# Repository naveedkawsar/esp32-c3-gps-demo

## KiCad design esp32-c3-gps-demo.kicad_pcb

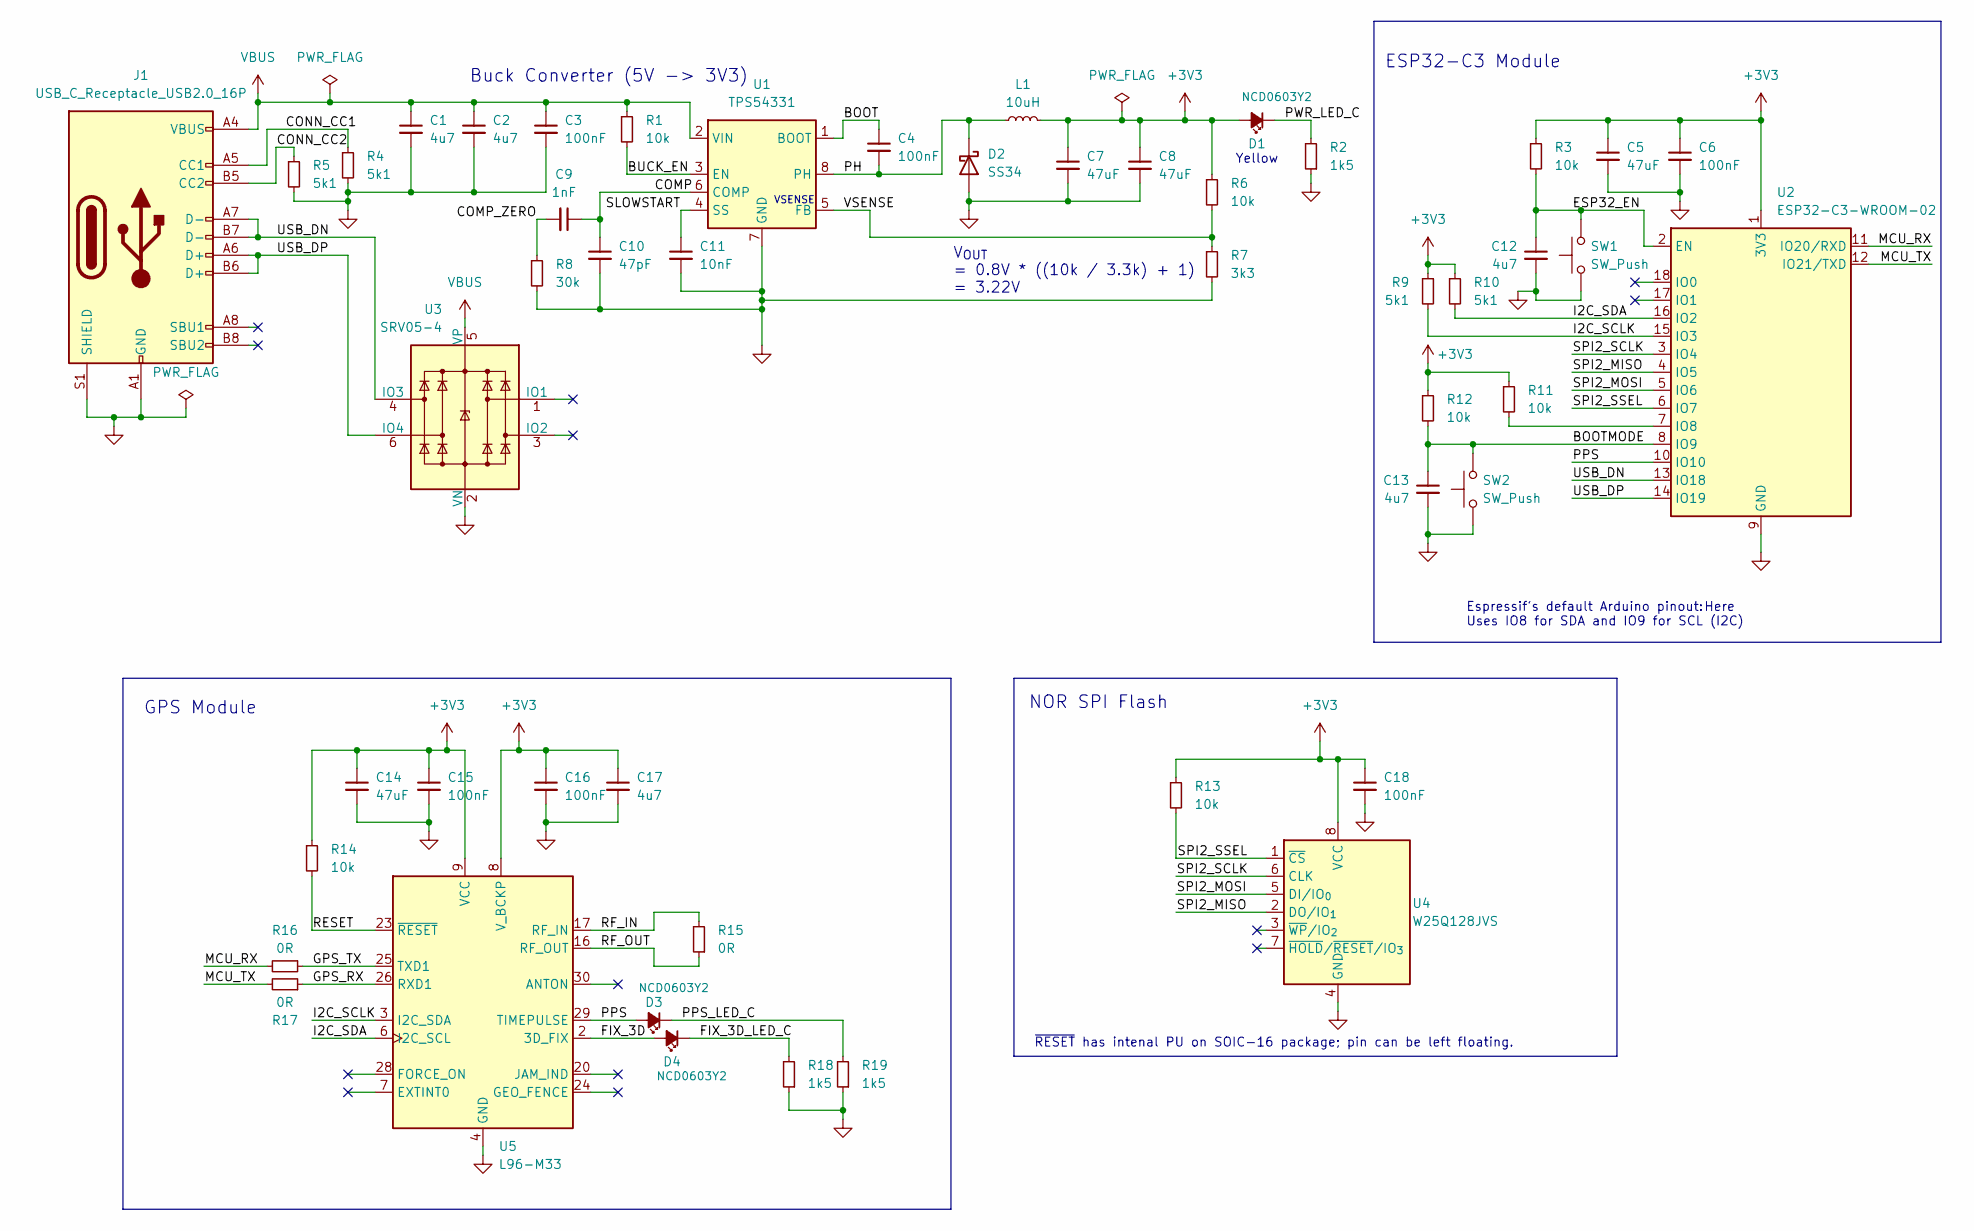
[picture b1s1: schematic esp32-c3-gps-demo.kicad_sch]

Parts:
C1, C2, C12, C13, C17: 4u7; C_0603_1608Metric; Voltage 16V; Manufacturer Part Number CL10A475KO8NNNC; LCSC Part # C19666
C3, C4, C6, C15, C16, C18: 100nF; C_0603_1608Metric; Voltage 50V; Manufacturer Part Number CC0603KRX7R9BB104; LCSC Part # C14663
C5, C7, C8, C14: 47uF; C_0805_2012Metric; Voltage 6V3; Manufacturer Part Number CL21A476MQYNNNE; LCSC Part # C16780
C9: 1nF; C_0603_1608Metric; Voltage 50V; Manufacturer Part Number CL10B102KB8NNNC; LCSC Part # C1588
C10: 47pF; C_0603_1608Metric; Voltage 50V; Manufacturer Part Number CL10C470JB8NNNC; LCSC Part # C1671
C11: 10nF; C_0603_1608Metric; Voltage 50V; Manufacturer Part Number 0603B103K500NT; LCSC Part # C57112
D1, D3, D4: NCD0603Y2; LED_0603_1608Metric; Manufacturer Part Number NCD0603Y2; LCSC Part # C89811
D2: SS34; D_SMA; LCSC Part # C8678
J1: USB_C_Receptacle_USB2.0_16P; USB_C_Receptacle_XKB_U262-16XN-4BVC11; Manufacturer Part Number U262-161N-4BVC11; LCSC Part # C319148
L1: 10uH; L_Changjiang_FXL0630; Manufacturer Part Number FXL0630-100-M; LCSC Part # C167223
R1, R3, R6, R11, R12, R13, R14: 10k; R_0603_1608Metric; Voltage 75V; Manufacturer Part Number 0603WAF1002T5E; LCSC Part # C25804
R2, R18, R19: 1k5; R_0603_1608Metric; Voltage 75V; Manufacturer Part Number 0603WAF1501T5E; LCSC Part # C22843
R4, R5, R9, R10: 5k1; R_0603_1608Metric; Voltage 75V; Manufacturer Part Number 0603WAF5101T5E; LCSC Part # C23186
R7: 3k3; R_0603_1608Metric; Voltage 75V; Manufacturer Part Number 0603WAF3301T5E; LCSC Part # C22978
R8: 30k; R_0603_1608Metric; Voltage 75V; Manufacturer Part Number 0603WAF3002T5E; LCSC Part # C22984
R15, R16, R17: 0R; R_0603_1608Metric; Voltage 75V; Manufacturer Part Number 0603WAF0000T5E; LCSC Part # C21189
SW1, SW2: SW_Push; SW_Push_1P1T_XKB_TS-1187A; LCSC Part # C318884
U1: TPS54331; SOIC-8_3.9x4.9mm_P1.27mm; LCSC Part # C9865
U2: ESP32-C3-WROOM-02; ESP32-C3-WROOM-02_NoVias; Manufacturer Part Number ESP32-C3-WROOM-02-N4; LCSC Part # C2934560
U3: SRV05-4; SOT-23-6; LCSC Part # C20615829
U4: W25Q128JVS; SOIC-8_5.23x5.23mm_P1.27mm; Manufacturer Part Number W25Q128JVSIQ; LCSC Part # C97521
U5: L96-M33; Quectel_L96

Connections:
+3V3: C5.1, C6.1, C7.1, C8.1, C14.1, C15.1, C16.1, C17.1, C18.1, D1.2 (A), L1.2, R3.1, R6.1, R9.1, R10.1, R11.1, R12.1, R13.1, R14.1, U2.1 (3V3), U4.8 (VCC), U5.8 (V_BCKP), U5.9 (VCC)
/BOOT: C4.1, U1.1 (BOOT)
/BOOTMODE: C13.1, R12.2, SW2.2, U2.8 (IO9)
/BUCK_EN: R1.2, U1.3 (EN)
/COMP: C9.1, C10.1, U1.6 (COMP)
/COMP_ZERO: C9.2, R8.1
/CONN_CC1: J1.A5 (CC1), R4.1
/CONN_CC2: J1.B5 (CC2), R5.1
/ESP32_EN: C12.1, R3.2, SW1.2, U2.2 (EN)
/FIX_3D: D4.2 (A), U5.2 (3D_FIX)
/FIX_3D_LED_C: D4.1 (K), R18.2
/GPS_RX: R17.1, U5.26 (RXD1)
/GPS_TX: R16.1, U5.25 (TXD1)
/I2C_SCLK: R9.2, U2.15 (IO3), U5.3 (I2C_SDA)
/I2C_SDA: R10.2, U2.16 (IO2), U5.6 (I2C_SCL)
/MCU_RX: R16.2, U2.11 (IO20/RXD)
/MCU_TX: R17.2, U2.12 (IO21/TXD)
/PH: C4.2, D2.1 (K), L1.1, U1.8 (PH)
/PPS: D3.2 (A), U2.10 (IO10), U5.29 (TIMEPULSE)
/PPS_LED_C: D3.1 (K), R19.2
/PWR_LED_C: D1.1 (K), R2.2
/RESET: R14.2, U5.23 (~RESET)
/RF_IN: R15.2, U5.17 (RF_IN)
/RF_OUT: R15.1, U5.16 (RF_OUT)
/SLOWSTART: C11.1, U1.4 (SS)
/SPI2_MISO: U2.4 (IO5), U4.2 (DO/IO_{1})
/SPI2_MOSI: U2.5 (IO6), U4.5 (DI/IO_{0})
/SPI2_SCLK: U2.3 (IO4), U4.6 (CLK)
/SPI2_SSEL: R13.2, U2.6 (IO7), U4.1 (~CS)
/USB_DN: J1.A7 (D-), J1.B7 (D-), U2.13 (IO18), U3.4 (IO3)
/USB_DP: J1.A6 (D+), J1.B6 (D+), U2.14 (IO19), U3.6 (IO4)
/VSENSE: R6.2, R7.1, U1.5 (FB)
GND: C1.2, C2.2, C3.2, C5.2, C6.2, C7.2, C8.2, C10.2, C11.2, C12.2, C13.2, C14.2, C15.2, C16.2, C17.2, C18.2, D2.2 (A), J1.A1 (GND), J1.A12 (GND), J1.B1 (GND), J1.B12 (GND), J1.S1 (SHIELD), R2.1, R4.2, R5.2, R7.2, R8.2, R18.1, R19.1, SW1.1, SW2.1, U1.7 (GND), U2.9 (GND), U2.19 (GND), U3.2 (VN), U4.4 (GND), U5.4 (GND), U5.5 (GND), U5.10 (GND), U5.11 (GND), U5.12 (GND), U5.13 (GND), U5.14 (GND), U5.15 (GND), U5.18 (GND), U5.19 (GND), U5.21 (GND), U5.22 (GND), U5.27 (GND), U5.31 (GND)
unnamed: R11.2, U2.7 (IO8)
VBUS: C1.1, C2.1, C3.1, J1.A4 (VBUS), J1.A9 (VBUS), J1.B4 (VBUS), J1.B9 (VBUS), R1.1, U1.2 (VIN), U3.5 (VP)

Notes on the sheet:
GPS Module
NOR SPI Flash
~{RESET} has intenal PU on SOIC-16 package; pin can be left floating.
Yellow
VSENSE
Espressif's default Arduino pinout: Uses IO8 for SDA and IO9 for SCL (I2C)
Here
Buck Converter (5V -> 3V3)
V_{OUT} = 0.8V * ((10k / 3.3k) + 1) = 3.22V
ESP32-C3 Module

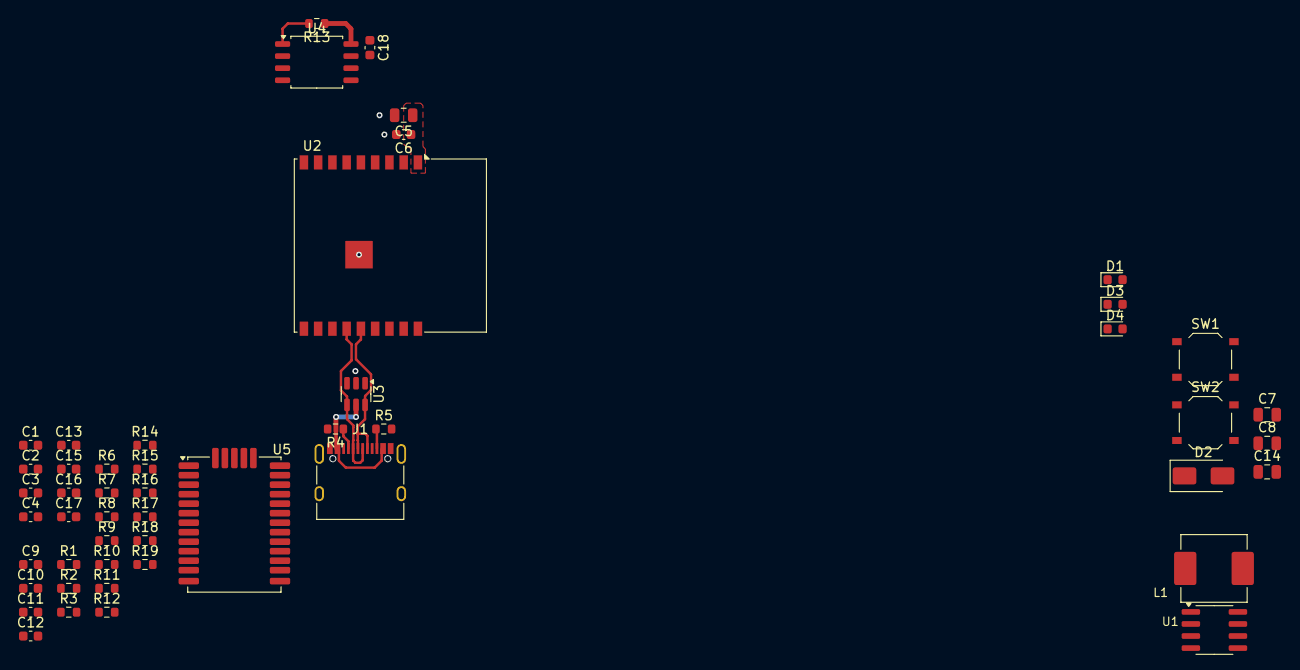
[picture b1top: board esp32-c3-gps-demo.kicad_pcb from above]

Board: 2 copper layers, 50 parts (0 on the bottom side), 35 nets.

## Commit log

2025-09-21 Initial version with completed schematic for USB connector, ESP32-C3 module, L96 GPS module, and SPI flash. To be drastically changed.
2025-09-22 Work in progress. Put down a mag sensor and EEPROM in schematic, but parts not finalized
2026-02-16 Put down an LIS3DH on the schematic without connections so as not to forget to use the accel
2026-05-11 Started adding battery circuitry to power the board from 1.5V. Added symbol and footprints for alternate magnetometer and GNSS modules
2026-05-12 Added ORing circuit for USB 5V and boost converter 5V
